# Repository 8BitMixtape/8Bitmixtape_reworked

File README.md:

# MixtapeNEO reworked
It's not really new... but finally fully working wiht KiCAD and svg2Shenzhen.
Reworked the "classic" 8Bit Mixtape NEO, now with new design, working amplifier 8002 and integrated speaker. Repsoitionend the battery holders, added holes for the speaker and improved the footprints hand-soldering.

## Fully redesigned version

Clone / fork this repo and make your own design!!

### Digilog Version

### Pixelache Version

A limited edition of the Pixelache 2019 Mixtape kits are available from Steve Maher, get in contact with hom on fbook: https://www.facebook.com/steve.maher.39

### Make your own Designs!

Modify it in other shapes, such as Eurorack? Make a really really small one? Simplfy it as a little sound toy?

### Print your own 3d-case

https://github.com/8BitMixtape/8Bitmixtape_reworked/blob/master/3d-case/MixTape_Case_VerMayl19_11.stl

## Soldering Instruction

Download printable .pdf here:

https://github.com/8BitMixtape/8Bitmixtape_reworked/blob/master/instructions/Digilog_Mixtape_partsplacement_v04.pdf

## KiCAD PCB and 3d View

## KiCAD complete schematic

## KiCAD dedicated footprints

Optimized footprints and 3d-models DONE. 

### To Add
* LiPo charge management
* (ISP connector)

## creative design layer in Inkscape with svg2shenzhen extension

Empty canvas in inkscape for creating all kind of creative PCB designs, edge.cut and drill layer taken from earlier editions. Use svg2shenzhen extension to export the footpring .kicad_mod to the dedicated footprint library.

See more about svg2shenzhen here: https://github.com/badgeek/svg2shenzhen

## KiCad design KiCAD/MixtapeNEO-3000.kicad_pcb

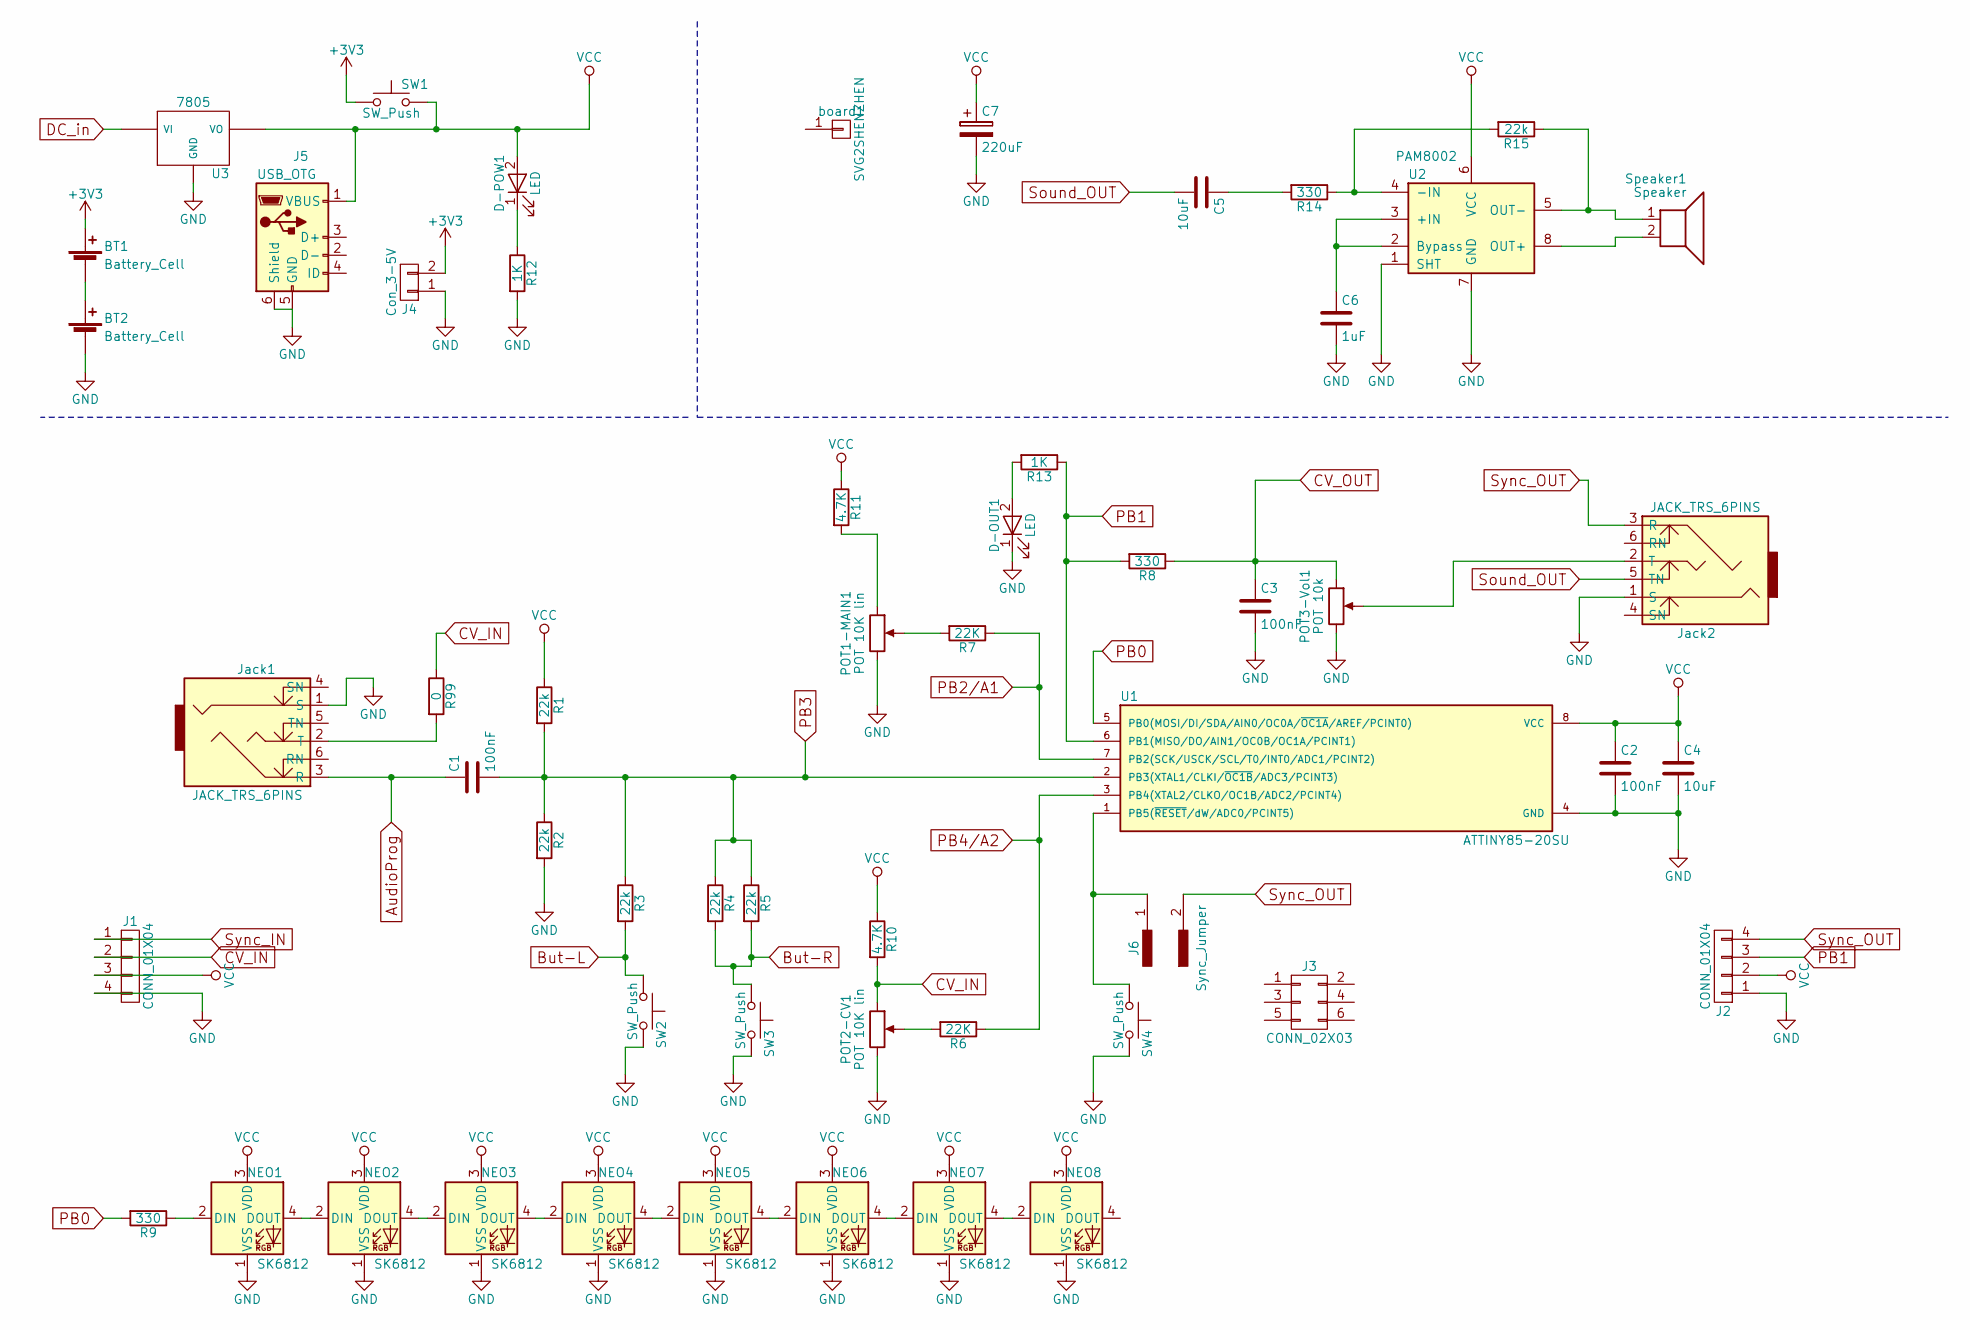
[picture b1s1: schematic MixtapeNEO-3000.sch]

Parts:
BT1, BT2: Battery_Cell; BAT_Holder_AAA-new_noHole
C1, C2, C3: 100nF; C_1206_HandSoldering
C4, C5: 10uF; C_1206_HandSoldering
C6: 1uF; C_1206_HandSoldering
C7: 220uF; C_1206_HandSoldering
D-OUT1: LED; LED_2835_minimal
D-POW1: LED; LED_2835_minimal
J1, J2: CONN_01X04; Angled_1x04_Pitch2.54mm-flip
J3: CONN_02X03; Socket_Strip_Straight_2x03_Pitch2.54mm
J4: Con_3-5V; Bat_connector_SMD
J5: USB_OTG; USB_Micro-B
J6: Sync_Jumper; Sync_jumper
Jack1, Jack2: JACK_TRS_6PINS; AUDIO-Jack_3.5mm_5Pin
NEO1, NEO2, NEO3, NEO4, NEO5, NEO6, NEO7, NEO8: SK6812; Mixtape_NEO_WS2812B
POT1-MAIN1, POT2-CV1: POT 10K lin; Potentiometer_backPads_noHole
POT3-Vol1: POT 10k; Potentiometer_wheel
R1, R2, R3, R4, R5, R15: 22k; R_1206_HandSoldering
R6, R7: 22K; R_1206_HandSoldering
R8, R9, R14: 330; R_1206_HandSoldering
R10, R11: 4.7K; R_1206_HandSoldering
R12, R13: 1K; R_1206_HandSoldering
R99: 0; R_1206_HandSoldering
SW1: SW_Push; Push_SWITCH_hole
SW2, SW3: SW_Push; TACTILE-PTH_6mm_SMD
SW4: SW_Push; SW_SPST_FSMSM
Speaker1: Speaker; SpeakerPads_SMD
U1: ATTINY85-20SU; Attiny_DIP-8_W7.62mm_mod
U2: PAM8002; SO-8_fixed
U3: 7805; TO-252-3_TabPin2
board1: SVG2SHENZHEN; Mixtape_reworked

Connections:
+3V3: BT1.1 (+), J4.2, SW1.1
AudioProg: C1.1, Jack1.3 (R)
But-L: R3.2, SW2.1
But-R: R4.2, R5.2, SW3.1
CV_IN: J1.2, POT2-CV1.1, R10.2, R99.1
CV_OUT: C3.1, POT3-Vol1.1, R8.1
GND: BT2.2 (-), C2.2, C3.2, C4.2, C6.2, C7.2, D-OUT1.1 (K), J1.4, J2.1, J4.1, J5.5 (GND), J5.6 (Shield), Jack1.1 (S), Jack2.1 (S), NEO1.1 (VSS), NEO2.1 (VSS), NEO3.1 (VSS), NEO4.1 (VSS), NEO5.1 (VSS), NEO6.1 (VSS), NEO7.1 (VSS), NEO8.1 (VSS), POT1-MAIN1.3, POT2-CV1.3, POT3-Vol1.3, R2.2, R12.2, SW2.2, SW3.2, SW4.2, U1.4 (GND), U2.1 (SHT), U2.7 (GND), U3.GND
unnamed: BT1.2 (-), BT2.1 (+)
unnamed: C5.1, R14.2
unnamed: C6.1, U2.2 (Bypass), U2.3 (+IN)
unnamed: D-OUT1.2 (A), R13.2
unnamed: D-POW1.1 (K), R12.1
unnamed: J6.1, SW4.1, U1.1 (PB5(~RESET~/dW/ADC0/PCINT5))
unnamed: Jack1.2 (T), R99.2
unnamed: Jack2.2 (T), POT3-Vol1.2
unnamed: NEO1.2 (DIN), R9.1
unnamed: NEO1.4 (DOUT), NEO2.2 (DIN)
unnamed: NEO2.4 (DOUT), NEO3.2 (DIN)
unnamed: NEO3.4 (DOUT), NEO4.2 (DIN)
unnamed: NEO4.4 (DOUT), NEO5.2 (DIN)
unnamed: NEO5.4 (DOUT), NEO6.2 (DIN)
unnamed: NEO6.4 (DOUT), NEO7.2 (DIN)
unnamed: NEO7.4 (DOUT), NEO8.2 (DIN)
unnamed: POT1-MAIN1.1, R11.2
unnamed: POT1-MAIN1.2, R7.2
unnamed: POT2-CV1.2, R6.2
unnamed: R14.1, R15.2, U2.4 (-IN)
unnamed: R15.1, Speaker1.1, U2.5 (OUT-)
unnamed: Speaker1.2, U2.8 (OUT+)
PB0: R9.2, U1.5 (PB0(MOSI/DI/SDA/AIN0/OC0A/~OC1A~/AREF/P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)
PB1: J2.3, R8.2, R13.1, U1.6 (PB1(MISO/DO/AIN1/OC0B/OC1A/PCINT1))
PB2/A1: R7.1, U1.7 (PB2(SCK/USCK/SCL/T0/INT0/ADC1/PCINT2))
PB3: C1.2, R1.2, R2.1, R3.1, R4.1, R5.1, U1.2 (PB3(XTAL1/CLKI/~OC1B~/ADC3/PCINT3))
PB4/A2: R6.1, U1.3 (PB4(XTAL2/CLKO/OC1B/ADC2/PCINT4))
Sound_OUT: C5.2, Jack2.5 (TN)
Sync_OUT: J2.4, J6.2, Jack2.3 (R)
VCC: C2.1, C4.1, C7.1, D-POW1.2 (A), J1.3, J2.2, J5.1 (VBUS), NEO1.3 (VDD), NEO2.3 (VDD), NEO3.3 (VDD), NEO4.3 (VDD), NEO5.3 (VDD), NEO6.3 (VDD), NEO7.3 (VDD), NEO8.3 (VDD), R1.1, R10.1, R11.1, SW1.2, U1.8 (VCC), U2.6 (VCC), U3.VO

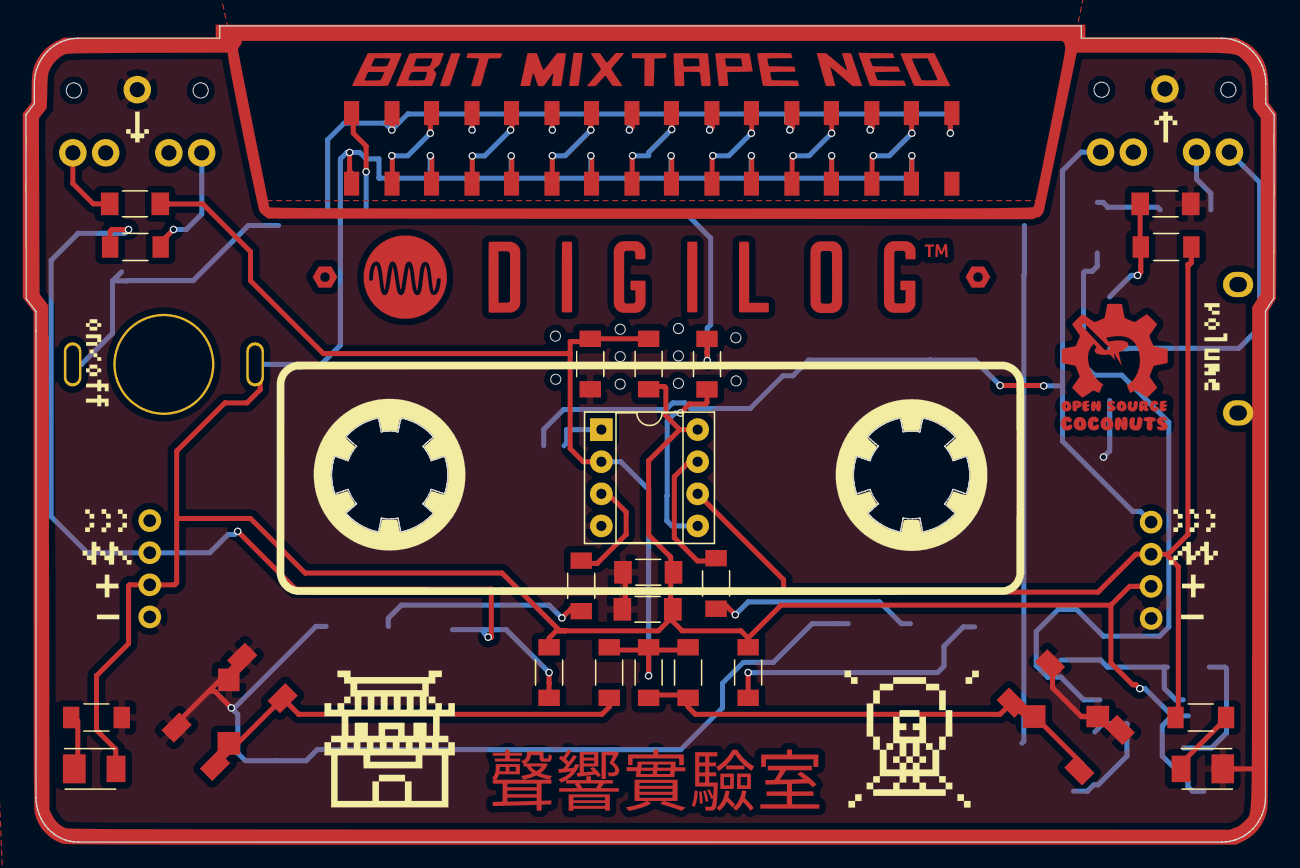
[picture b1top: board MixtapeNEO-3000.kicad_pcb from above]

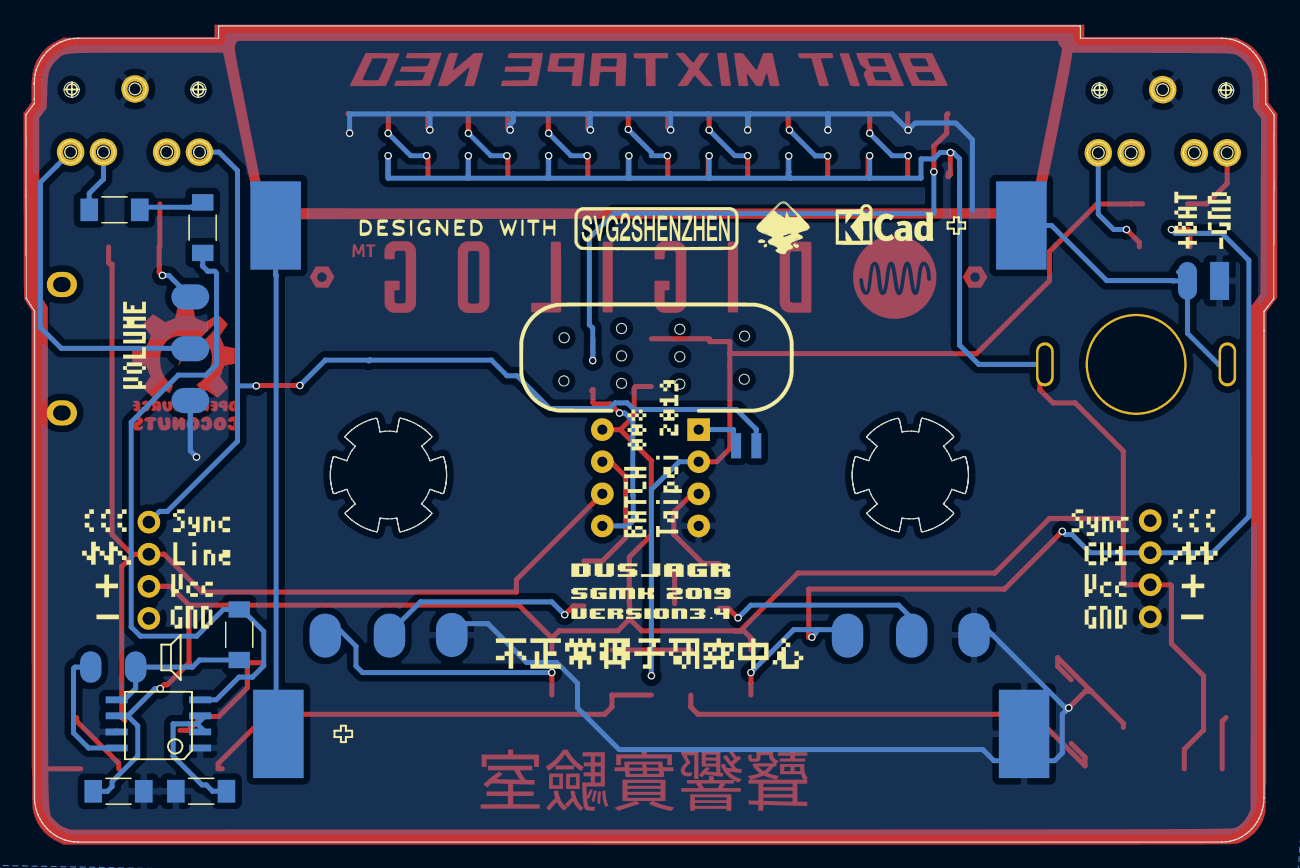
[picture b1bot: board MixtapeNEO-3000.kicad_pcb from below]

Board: 2 copper layers, 98.8 x 64.6 mm, 55 parts (19 on the bottom side), 37 nets.

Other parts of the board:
Ref**: Val**; dusjagr
Ref**#2: Val**; Coconut_logo_sm
Ref**#3: Val**; CACR_chinese_hori
Ref**#4: Val**; MadeInTaiwan_sm

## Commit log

2019-05-01 adding files
2019-05-01 adding more description
2019-05-11 reworked kicad 5 and many new design
2019-05-18 moved 3d case here, now with 'click'
2019-05-18 adding photos
2019-05-18 adding partsPlacement
2019-11-21 adding photos of all PCBs
